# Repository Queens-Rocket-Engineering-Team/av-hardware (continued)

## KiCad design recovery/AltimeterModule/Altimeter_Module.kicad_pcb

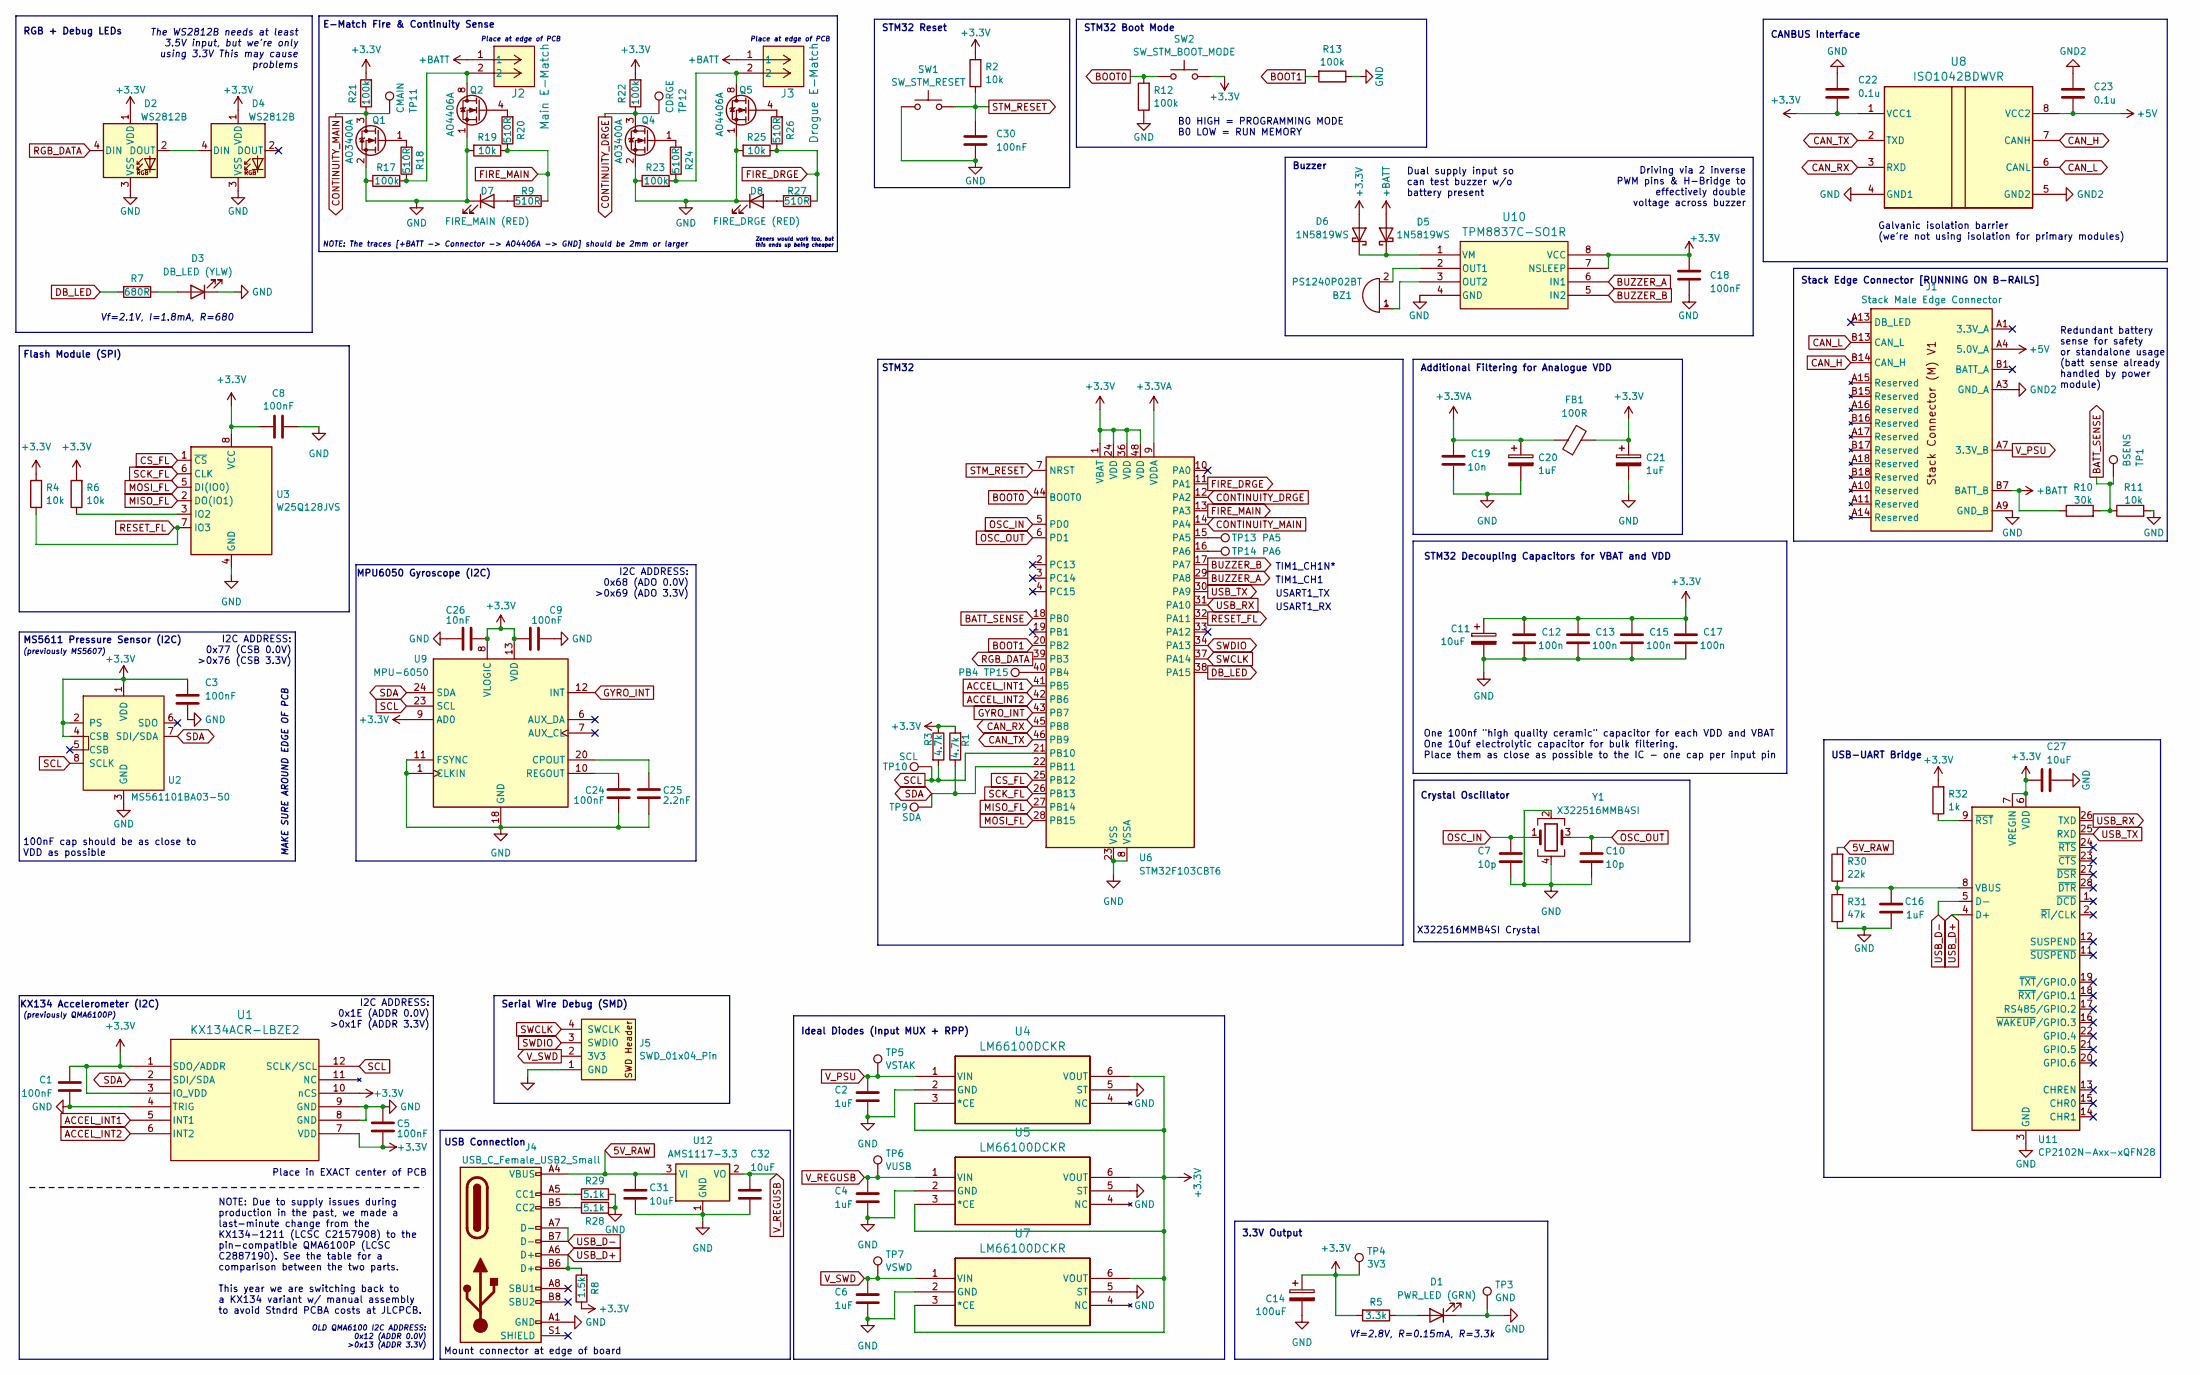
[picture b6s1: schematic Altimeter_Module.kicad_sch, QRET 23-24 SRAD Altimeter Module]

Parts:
BZ1: PS1240P02BT; Buzzer_12.6x9.5RM5.0; Digikey 445-2525-1-ND
C1, C3, C5, C8, C9, C18, C24, C30: 100nF; C_0603_1608Metric; JLCPCB C14663
C2, C4, C6, C16: 1uF; C_0603_1608Metric; JLCPCB C15849
C7, C10: 10p; C_0603_1608Metric; JLCPCB C1634
C11: 10uF; CP_Elec_4x5.4; Digikey 732-8411-1-ND
C12, C13, C15, C17: 100n; C_0402_1005Metric; JLCPCB C1525
C14: 100uF; CP_Elec_6.3x5.9; Digikey 732-8419-1-ND
C19: 10n; C_0603_1608Metric; JLCPCB C57112
C20, C21: 1uF; C_0805_2012Metric; JLCPCB C28323
C22, C23: 0.1u; C_0603_1608Metric; JLCPCB C14663
C25: 2.2nF; C_0603_1608Metric; JLCPCB C1604
C26: 10nF; C_0603_1608Metric; JLCPCB C57112
C27, C31, C32: 10uF; C_0603_1608Metric; JLCPCB C96446
D1: PWR_LED (GRN); LED_0805_2012Metric; JLCPCB C2297
D2, D4: WS2812B; LED_WS2812B_PLCC4_5.0x5.0mm_P3.2mm; Digikey 1568-COM-16347CT-ND
D3: DB_LED (YLW); LED_0603_1608Metric; JLCPCB C72038
D5, D6: 1N5819WS; D_SOD-323; JLCPCB C191023
D7: FIRE_MAIN (RED); LED_0603_1608Metric; JLCPCB C2286
D8: FIRE_DRGE (RED); LED_0603_1608Metric; JLCPCB C2286
FB1: 100R; R_0805_2012Metric; JLCPCB C1015
J1: Stack Male Edge Connector; BUS_PCIexpress_x1
J2: Main E-Match; CONN_2-1445057-2_TYCO; Digikey A33212CT-ND
J3: Drogue E-Match; CONN_2-1445057-2_TYCO; Digikey A33212CT-ND
J4: USB_C_Female_USB2_Small; USB_C_DB-108PWB; JLCPCB C5178541
J5: SWD_01x04_Pin; SWD_PinHeader_1x04_P2.54mm_Horizontal_SMD; Digikey 952-3233-ND
Q1, Q4: AO3400A; SOT-23; JLCPCB C20917
Q2, Q5: AO4406A; SOIC-8_3.9x4.9mm_P1.27mm; JLCPCB C5155213
R1, R3: 4.7k; R_0603_1608Metric; JLCPCB C23162
R2, R4, R6, R11, R19, R25: 10k; R_0603_1608Metric; JLCPCB C25804
R5: 3.3k; R_0603_1608Metric; JLCPCB C22978
R7: 680R; R_0603_1608Metric; JLCPCB C23228
R8: 1.5k; R_0603_1608Metric; JLCPCB C22843
R9, R18, R20, R24, R26, R27: 510R; R_0603_1608Metric; JLCPCB C23193
R10: 30k; R_0603_1608Metric; JLCPCB C22984
R12, R13, R17, R21, R22, R23: 100k; R_0603_1608Metric; JLCPCB C25803
R28, R29: 5.1k; R_0603_1608Metric; JLCPCB C23186
R30: 22k; R_0603_1608Metric; JLCPCB C31850
R31: 47k; R_0603_1608Metric; JLCPCB C25819
R32: 1k; R_0603_1608Metric; JLCPCB C21190
SW1: SW_STM_RESET; SW_Push_1P1T_XKB_TS-1187A; JLCPCB C318884
SW2: SW_STM_BOOT_MODE; SW_Push_1P1T_XKB_TS-1187A; JLCPCB C318884
TP1: BSENS; TestPoint_Pad_1.5x1.5mm
TP3: GND; TestPoint_Pad_1.5x1.5mm
TP4: 3V3; TestPoint_Pad_1.5x1.5mm
TP5: VSTAK; TestPoint_Pad_1.5x1.5mm
TP6: VUSB; TestPoint_Pad_1.5x1.5mm
TP7: VSWD; TestPoint_Pad_1.5x1.5mm
TP9: SDA; TestPoint_Pad_1.5x1.5mm
TP10: SCL; TestPoint_Pad_1.5x1.5mm
TP11: CMAIN; TestPoint_Pad_1.5x1.5mm
TP12: CDRGE; TestPoint_Pad_1.5x1.5mm
TP13: PA5; TestPoint_Pad_1.5x1.5mm
TP14: PA6; TestPoint_Pad_1.5x1.5mm
TP15: PB4; TestPoint_Pad_1.5x1.5mm
U1: KX134ACR-LBZE2; LGA-12_2x2mm_P0.5mm; Digikey 846-KX134ACR-LBZE2CT-ND
U2: MS561101BA03-50; MS5607_Handsolder; Digikey 223-1622-1-ND
U3: W25Q128JVS; SOIC-8_5.23x5.23mm_P1.27mm; JLCPCB C97521
U4, U5, U7: LM66100DCKR; SC-70-6_Handsoldering; JLCPCB C2869734
U6: STM32F103CBT6; LQFP-48_7x7mm_P0.5mm; JLCPCB C8304
U8: ISO1042BDWVR; SOIC-8 ISO1042BDWV; JLCPCB C484409
U9: MPU-6050; InvenSense_QFN-24_4x4mm_P0.5mm; JLCPCB C24112
U10: TPM8837C-SO1R; SOP-8_TPK; Digikey 5503-TPM8837C-SO1RCT-ND
U11: CP2102N-Axx-xQFN28; QFN-28-1EP_5x5mm_P0.5mm_EP3.35x3.35mm; JLCPCB C6568
U12: AMS1117-3.3; SOT-223-3_TabPin2; JLCPCB C6186
Y1: X322516MMB4SI; Crystal_SMD_3225-4Pin_3.2x2.5mm; JLCPCB C13738

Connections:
5V_RAW: C31.1, J4.A4 (VBUS), J4.A9 (VBUS), J4.B4 (VBUS), J4.B9 (VBUS), R30.2, U12.3 (VI)
+3.3V: C1.1, C3.1, C5.2, C8.1, C9.1, C11.1, C12.1, C13.1, C14.1, C15.1, C17.1, C18.1, C21.1, C22.2, C26.1, C27.2, D2.1 (VDD), D4.1 (VDD), D6.2 (A), FB1.2, R1.2, R2.2, R3.1, R4.2, R5.2, R6.2, R8.1, R21.2, R22.2, R32.2, SW2.2, TP4.1, U1.1 (SDO/ADDR), U1.3 (IO_VDD), U1.7 (VDD), U1.10 (nCS), U2.1 (VDD), U2.2 (PS), U2.4 (CSB), U3.8 (VCC), U4.3 (*CE), U4.6 (VOUT), U5.3 (*CE), U5.6 (VOUT), U6.1 (VBAT), U6.24 (VDD), U6.36 (VDD), U6.48 (VDD), U7.3 (*CE), U7.6 (VOUT), U8.1 (VCC1), U9.8 (VLOGIC), U9.9 (AD0), U9.13 (VDD), U10.7 (NSLEEP), U10.8 (VCC), U11.6 (VDD), U11.7 (VREGIN)
+3.3VA: C19.1, C20.1, FB1.1, U6.9 (VDDA)
+5V: C23.2, J1.A4 (5.0V_A), J1.A5 (5.0V_A), U8.8 (VCC2)
+BATT: D5.2 (A), J1.B7 (BATT_B), J1.B8 (BATT_B), J1.B9 (BATT_B), J2.1, J3.1, R10.1
ACCEL_INT1: U1.5 (INT1), U6.41 (PB5)
ACCEL_INT2: U1.6 (INT2), U6.42 (PB6)
BATT_SENSE: R10.2, R11.1, TP1.1, U6.18 (PB0)
BOOT0: R12.2, SW2.1, U6.44 (BOOT0)
BOOT1: R13.2, U6.20 (PB2)
BUZZER_A: U6.29 (PA8), U10.6 (IN1)
BUZZER_B: U6.17 (PA7), U10.5 (IN2)
CAN_H: J1.B14 (CAN_H), U8.7 (CANH)
CAN_L: J1.B13 (CAN_L), U8.6 (CANL)
CAN_RX: U6.45 (PB8), U8.3 (RXD)
CAN_TX: U6.46 (PB9), U8.2 (TXD)
CONTINUITY_DRGE: Q4.3 (D), R22.1, TP12.1, U6.12 (PA2)
CONTINUITY_MAIN: Q1.3 (D), R21.1, TP11.1, U6.14 (PA4)
CS_FL: U3.1 (~CS), U6.25 (PB12)
DB_LED: R7.2, U6.38 (PA15)
FIRE_DRGE: R25.1, R26.1, R27.1, U6.11 (PA1)
FIRE_MAIN: R9.1, R19.1, R20.1, U6.13 (PA3)
GND: C1.2, C2.2, C3.2, C4.2, C5.1, C6.2, C7.2, C8.2, C9.2, C10.2, C11.2, C12.2, C13.2, C14.2, C15.2, C16.1, C17.2, C18.2, C19.2, C20.2, C21.2, C22.1, C24.2, C25.2, C26.2, C27.1, C30.2, C31.2, C32.2, D1.1 (K), D2.3 (VSS), D3.1 (K), D4.3 (VSS), D7.1 (K), D8.1 (K), J1.A9 (GND_B), J1.A12 (GND_B), J1.B10 (GND_B), J1.B11 (GND_B), J1.B12 (GND_B), J4.A1 (GND), J4.A12 (GND), J4.B1 (GND), J4.B12 (GND), J5.1 (GND), Q1.2 (S), Q2.1 (S), Q2.2 (S), Q2.3 (S), Q4.2 (S), Q5.1 (S), Q5.2 (S), Q5.3 (S), R11.2, R12.1, R13.1, R17.1, R19.2, R23.1, R25.2, R28.2, R29.2, R31.1, SW1.1, TP3.1, U1.4 (TRIG), U1.8 (GND), U1.9 (GND), U2.3 (GND), U3.4 (GND), U4.2 (GND), U4.5 (ST), U5.2 (GND), U5.5 (ST), U6.8 (VSSA), U6.23 (VSS), U6.35 (VSS), U6.47 (VSS), U7.2 (GND), U7.5 (ST), U8.4 (GND1), U9.1 (CLKIN), U9.11 (FSYNC), U9.18 (GND), U10.4 (GND), U11.3 (GND), U11.29 (GND), U12.1 (GND), Y1.2, Y1.4
GND2: C23.1, J1.A3 (GND_A), J1.A6 (GND_A), J1.B4 (GND_A), J1.B5 (GND_A), J1.B6 (GND_A), U8.5 (GND2)
GYRO_INT: U6.43 (PB7), U9.12 (INT)
MISO_FL: U3.2 (DO(IO1)), U6.27 (PB14)
MOSI_FL: U3.5 (DI(IO0)), U6.28 (PB15)
unnamed: BZ1.2 (+), U10.2 (OUT1)
unnamed: BZ1.1 (-), U10.3 (OUT2)
unnamed: D1.2 (A), R5.1
unnamed: D2.2 (DOUT), D4.4 (DIN)
unnamed: D3.2 (A), R7.1
unnamed: D5.1 (K), D6.1 (K), U10.1 (VM)
unnamed: D7.2 (A), R9.2
unnamed: D8.2 (A), R27.2
unnamed: J2.2, Q2.5 (D), Q2.6 (D), Q2.7 (D), Q2.8 (D), R17.2, R18.1
unnamed: J3.2, Q5.5 (D), Q5.6 (D), Q5.7 (D), Q5.8 (D), R23.2, R24.1
unnamed: J4.A5 (CC1), R29.1
unnamed: J4.B5 (CC2), R28.1
unnamed: Q1.1 (G), R18.2
unnamed: Q2.4 (G), R20.2
unnamed: Q4.1 (G), R24.2
unnamed: Q5.4 (G), R26.2
unnamed: R6.1, U3.3 (IO2)
unnamed: TP13.1, U6.15 (PA5)
unnamed: TP14.1, U6.16 (PA6)
unnamed: TP15.1, U6.40 (PB4)
unnamed: C25.1, U9.20 (CPOUT)
unnamed: C24.1, U9.10 (REGOUT)
unnamed: C16.2, R30.1, R31.2, U11.8 (VBUS)
unnamed: R32.1, U11.9 (~RST)
OSC_IN: C7.1, U6.5 (PD0), Y1.1
OSC_OUT: C10.1, U6.6 (PD1), Y1.3
RESET_FL: R4.1, U3.7 (IO3), U6.32 (PA11)
RGB_DATA: D2.4 (DIN), U6.39 (PB3)
SCK_FL: U3.6 (CLK), U6.26 (PB13)
SCL: R3.2, TP10.1, U1.12 (SCLK/SCL), U2.8 (SCLK), U6.21 (PB10), U9.23 (SCL)
SDA: R1.1, TP9.1, U1.2 (SDI/SDA), U2.7 (SDI/SDA), U6.22 (PB11), U9.24 (SDA)
STM_RESET: C30.1, R2.1, SW1.2, U6.7 (NRST)
SWCLK: J5.4 (SWCLK), U6.37 (PA14)
SWDIO: J5.3 (SWDIO), U6.34 (PA13)
USB_D+: J4.A6 (D+), J4.B6 (D+), R8.2, U11.4 (D+)
USB_D-: J4.A7 (D-), J4.B7 (D-), U11.5 (D-)
USB_RX: U6.31 (PA10), U11.26 (TXD)
USB_TX: U6.30 (PA9), U11.25 (RXD)
V_PSU: C2.1, J1.A7 (3.3V_B), J1.A8 (3.3V_B), TP5.1, U4.1 (VIN)
V_REGUSB: C4.1, C32.1, TP6.1, U5.1 (VIN), U12.2 (VO)
V_SWD: C6.1, J5.2 (3V3), TP7.1, U7.1 (VIN)

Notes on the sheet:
Serial Wire Debug (SMD)
Flash Module (SPI)
RGB + Debug LEDs
The WS2812B needs at least 3.5V input, but we're only using 3.3V This may cause problems
Additional Filtering for Analogue VDD
(previously QMA6100P)
Stack Edge Connector [RUNNING ON B-RAILS]
NOTE: Due to supply issues during production in the past, we made a last-minute change from the KX134-1211 (LCSC C2157908) to the pin-compatible QMA6100P (LCSC C2887190). See the table for a comparison between the two parts. This year we are switching back to a KX134 variant w/ manual assembly to a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
Buzzer
Place at edge of PCB
Ideal Diodes (Input MUX + RPP)
Crystal Oscillator
Vf=2.1V, I=1.8mA, R=680
STM32
I2C ADDRESS: 0x1E (ADDR 0.0V) >0x1F (ADDR 3.3V)
B0 HIGH = PROGRAMMING MODE B0 LOW = RUN MEMORY
USART1_TX
USART1_RX
MS5611 Pressure Sensor (I2C)
Place in EXACT center of PCB
3.3V Output
OLD QMA6100 I2C ADDRESS: 0x12 (ADDR 0.0V) >0x13 (ADDR 3.3V)
Mount connector at edge of board
(previously MS5607)
X322516MMB4SI Crystal
CANBUS Interface
STM32 Decoupling Capacitors for VBAT and VDD
I2C ADDRESS: 0x68 (ADO 0.0V) >0x69 (ADO 3.3V)
STM32 Boot Mode
TIM1_CH1N*
TIM1_CH1
KX134 Accelerometer (I2C)
E-Match Fire & Continuity Sense
Galvanic isolation barrier (we're not using isolation for primary modules)
One 100nf "high quality ceramic" capacitor for each VDD and VBAT One 10uf electrolytic capacitor for bulk filtering. Place them as close as possible to the IC - one cap per input pin
NOTE: The traces [+BATT -> Connector -> AO4406A -> GND] should be 2mm or larger
Zeners would work too, but this ends up being cheaper
MAKE SURE AROUND EDGE OF PCB
Driving via 2 inverse PWM pins & H-Bridge to effectively double voltage across buzzer
100nF cap should be as close to VDD as possible

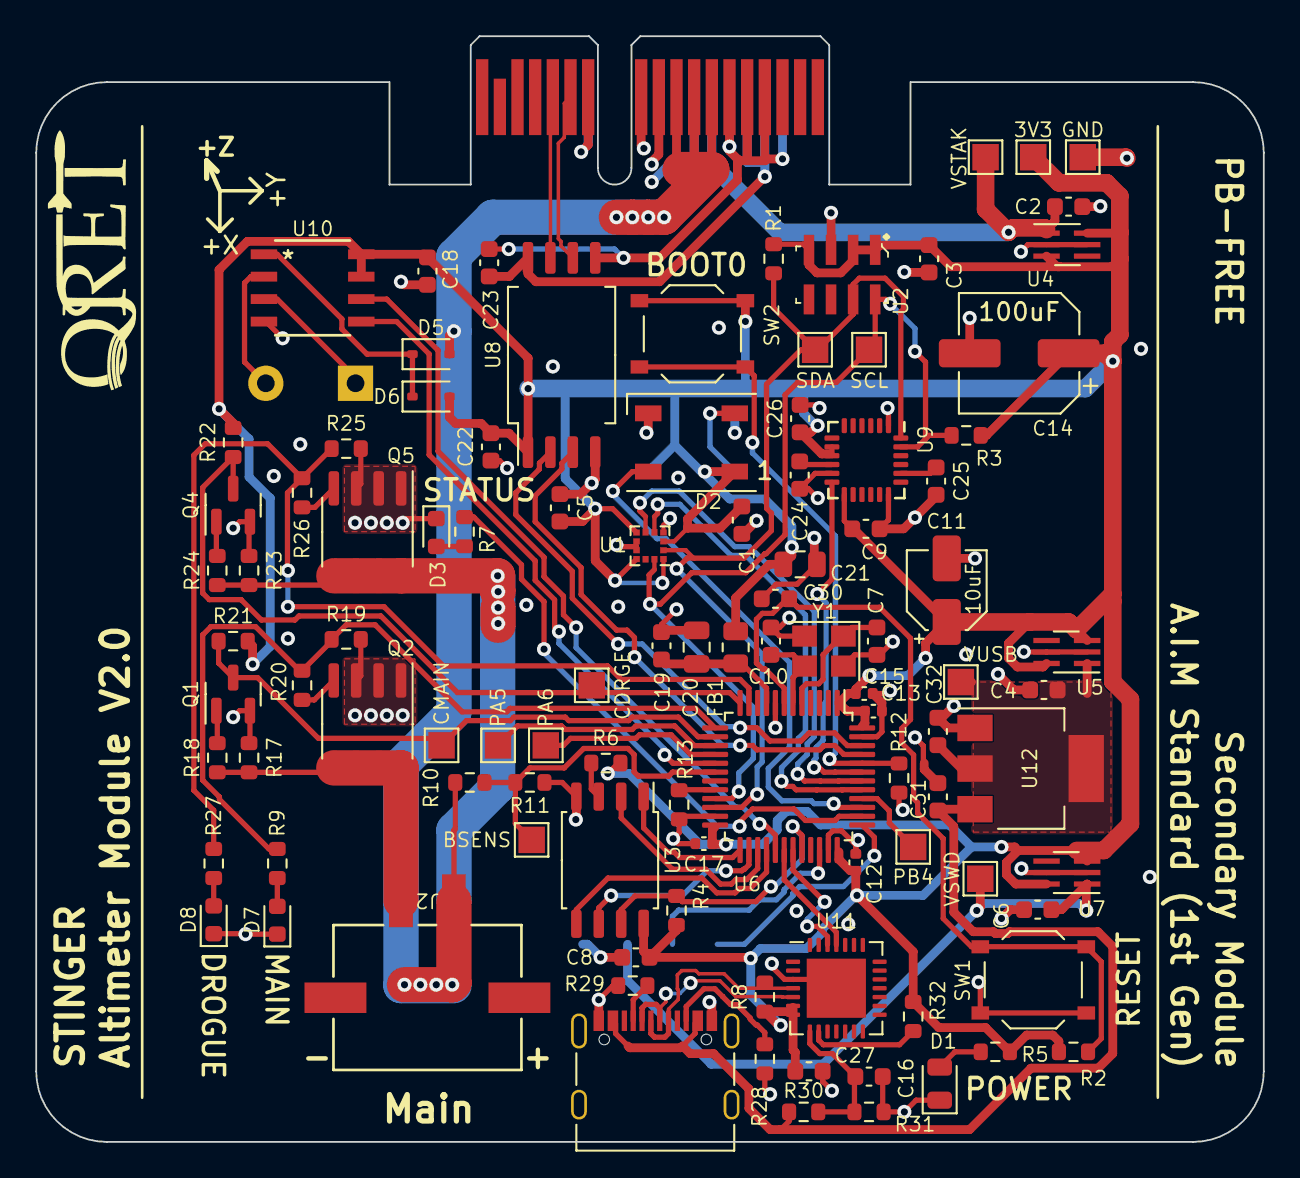
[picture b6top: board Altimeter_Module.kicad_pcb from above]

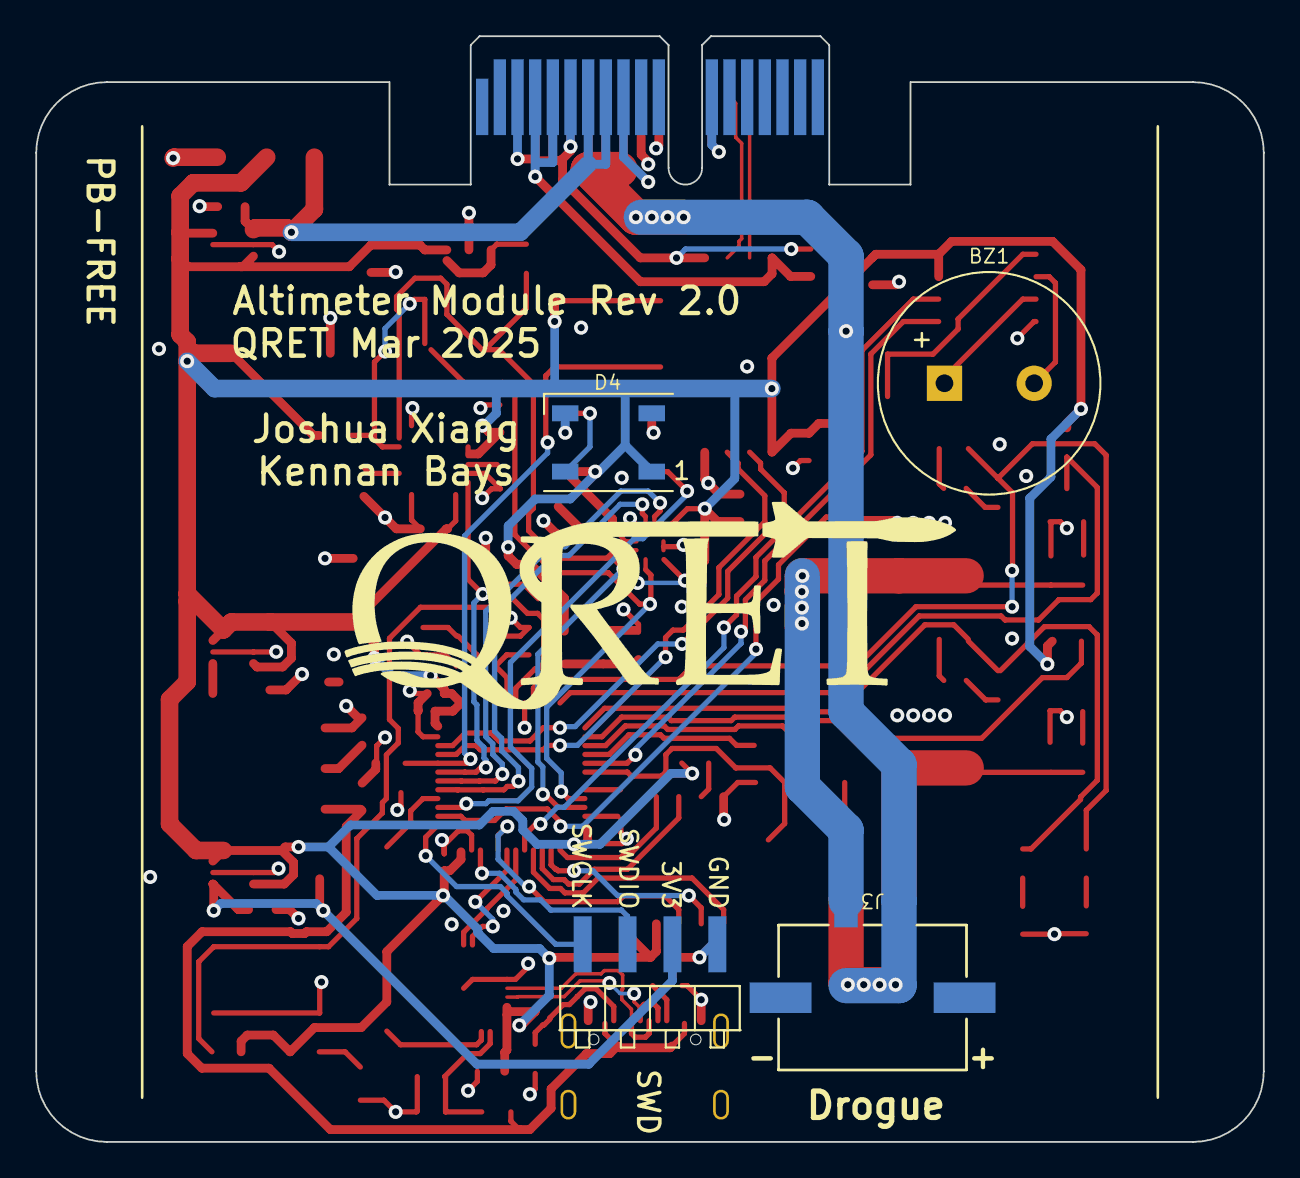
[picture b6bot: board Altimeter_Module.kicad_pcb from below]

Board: 4 copper layers, 69.5 x 62.6 mm, 106 parts (4 on the bottom side), 68 nets.

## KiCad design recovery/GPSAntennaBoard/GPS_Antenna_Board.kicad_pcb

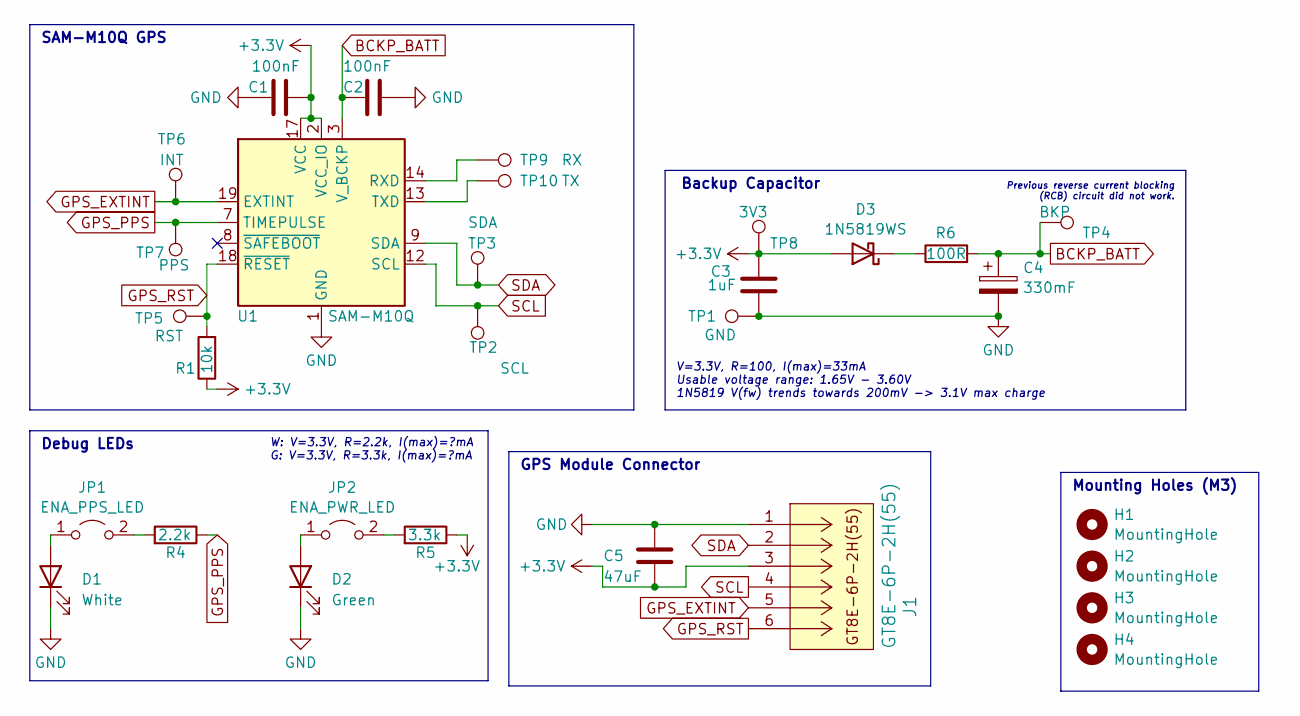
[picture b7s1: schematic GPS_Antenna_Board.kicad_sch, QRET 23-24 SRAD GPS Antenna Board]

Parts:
C1, C2: 100nF; C_0603_1608Metric; JLCPCB C14663
C3: 1uF; C_0603_1608Metric; JLCPCB C15849
C4: 330mF; CB5R5334HF-ZJP; Digikey 4688-CB5R5334HF-ZJP-ND
C5: 47uF; C_0805_2012Metric; JLCPCB C16780
D1: White; LED_0805_2012Metric; JLCPCB C34499
D2: Green; LED_0805_2012Metric; JLCPCB C2297
D3: 1N5819WS; D_SOD-323_HandSoldering; JLCPCB C191023
H1, H2, H3, H4: MountingHole; MountingHole_3.2mm_M3_DIN965_Pad
J1: GT8E-6P-2H(55); CONN_GT8E-6P-2H(55); Digikey 26-GT8E-6P-2H(55)CT-ND
JP1: ENA_PPS_LED; SolderJumper-2_P1.3mm_Open_RoundedPad1.0x1.5mm
JP2: ENA_PWR_LED; SolderJumper-2_P1.3mm_Open_RoundedPad1.0x1.5mm
R1: 10k; R_0603_1608Metric; JLCPCB C25804
R4: 2.2k; R_0603_1608Metric; JLCPCB C4190
R5: 3.3k; R_0603_1608Metric; JLCPCB C22978
R6: 100R; R_0603_1608Metric; JLCPCB C22775
TP1: GND; TestPoint_Pad_1.5x1.5mm
TP2: SCL; TestPoint_Pad_1.5x1.5mm
TP3: SDA; TestPoint_Pad_1.5x1.5mm
TP4: BKP; TestPoint_Pad_1.5x1.5mm
TP5: RST; TestPoint_Pad_1.5x1.5mm
TP6: INT; TestPoint_Pad_1.5x1.5mm
TP7: PPS; TestPoint_Pad_1.5x1.5mm
TP8: 3V3; TestPoint_Pad_1.5x1.5mm
TP9: RX; TestPoint_Pad_1.5x1.5mm
TP10: TX; TestPoint_Pad_1.5x1.5mm
U1: SAM-M10Q; ublox_SAM-M8Q_HandSolder; Digikey 672-SAM-M10Q-00BCT-ND

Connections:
+3.3V: C1.2, C3.1, C5.2, D3.2 (A), J1.3, R1.1, R5.1, TP8.1, U1.2 (VCC_IO), U1.17 (VCC)
BCKP_BATT: C2.2, C4.1, R6.2, TP4.1, U1.3 (V_BCKP)
GND: C1.1, C2.1, C3.2, C4.2, C5.1, D1.1 (K), D2.1 (K), J1.1, TP1.1, U1.1 (GND), U1.4 (GND), U1.5 (GND), U1.6 (GND), U1.10 (GND), U1.11 (GND), U1.15 (GND), U1.16 (GND), U1.20 (GND)
GPS_EXTINT: J1.5, TP6.1, U1.19 (EXTINT)
GPS_PPS: R4.1, TP7.1, U1.7 (TIMEPULSE)
GPS_RST: J1.6, R1.2, TP5.1, U1.18 (~RESET)
unnamed: D1.2 (A), JP1.1 (A)
unnamed: D2.2 (A), JP2.1 (A)
unnamed: D3.1 (K), R6.1
unnamed: JP1.2 (B), R4.2
unnamed: JP2.2 (B), R5.2
unnamed: TP9.1, U1.14 (RXD)
unnamed: TP10.1, U1.13 (TXD)
SCL: J1.4, TP2.1, U1.12 (SCL)
SDA: J1.2, TP3.1, U1.9 (SDA)

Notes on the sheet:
W: V=3.3V, R=2.2k, I(max)=?mA G: V=3.3V, R=3.3k, I(max)=?mA
Mounting Holes (M3)
V=3.3V, R=100, I(max)=33mA Usable voltage range: 1.65V - 3.60V 1N5819 V(fw) trends towards 200mV -> 3.1V max charge
Backup Capacitor
SAM-M10Q GPS
GPS Module Connector
Debug LEDs
Previous reverse current blocking (RCB) circuit did not work.

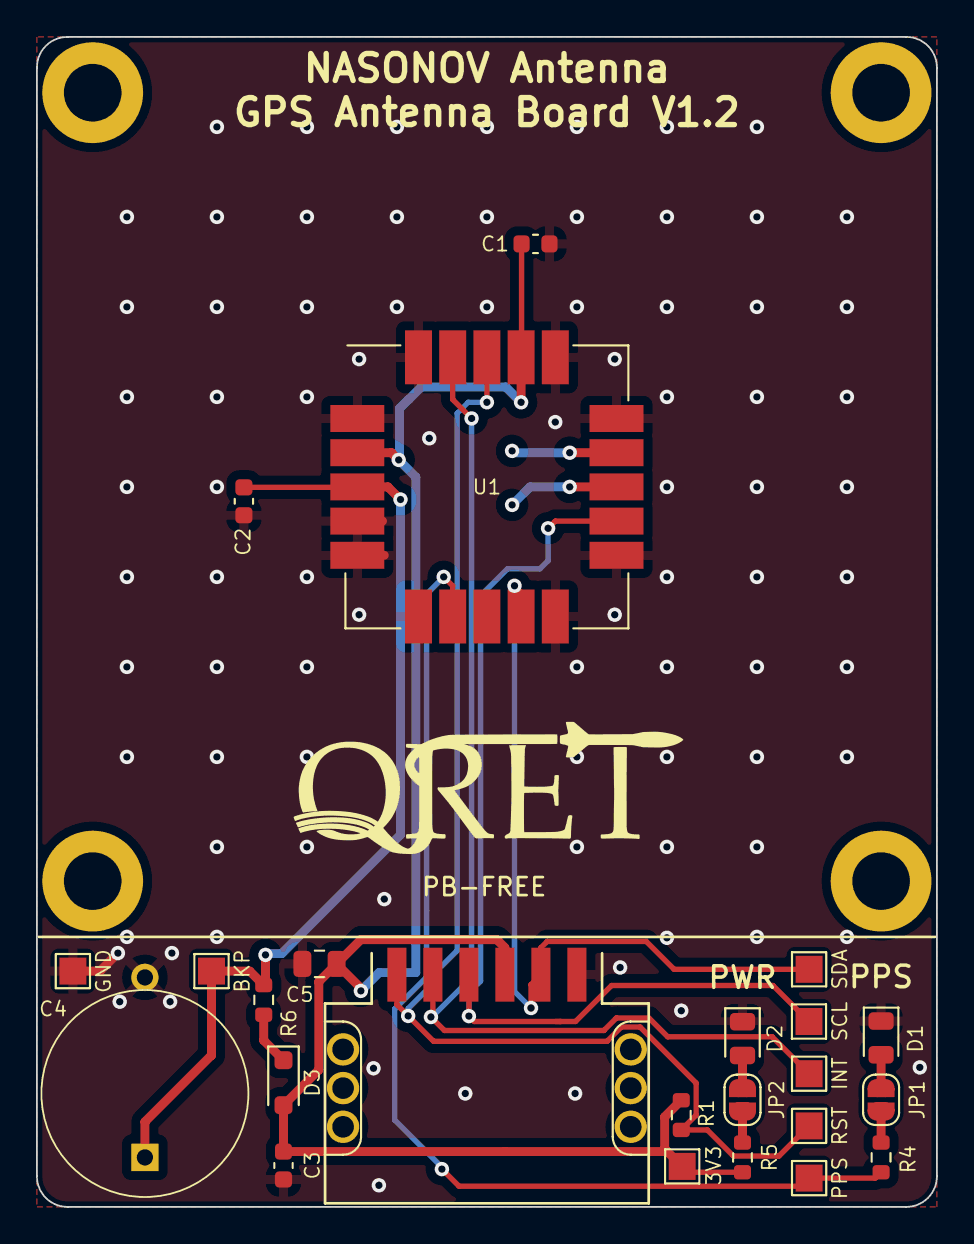
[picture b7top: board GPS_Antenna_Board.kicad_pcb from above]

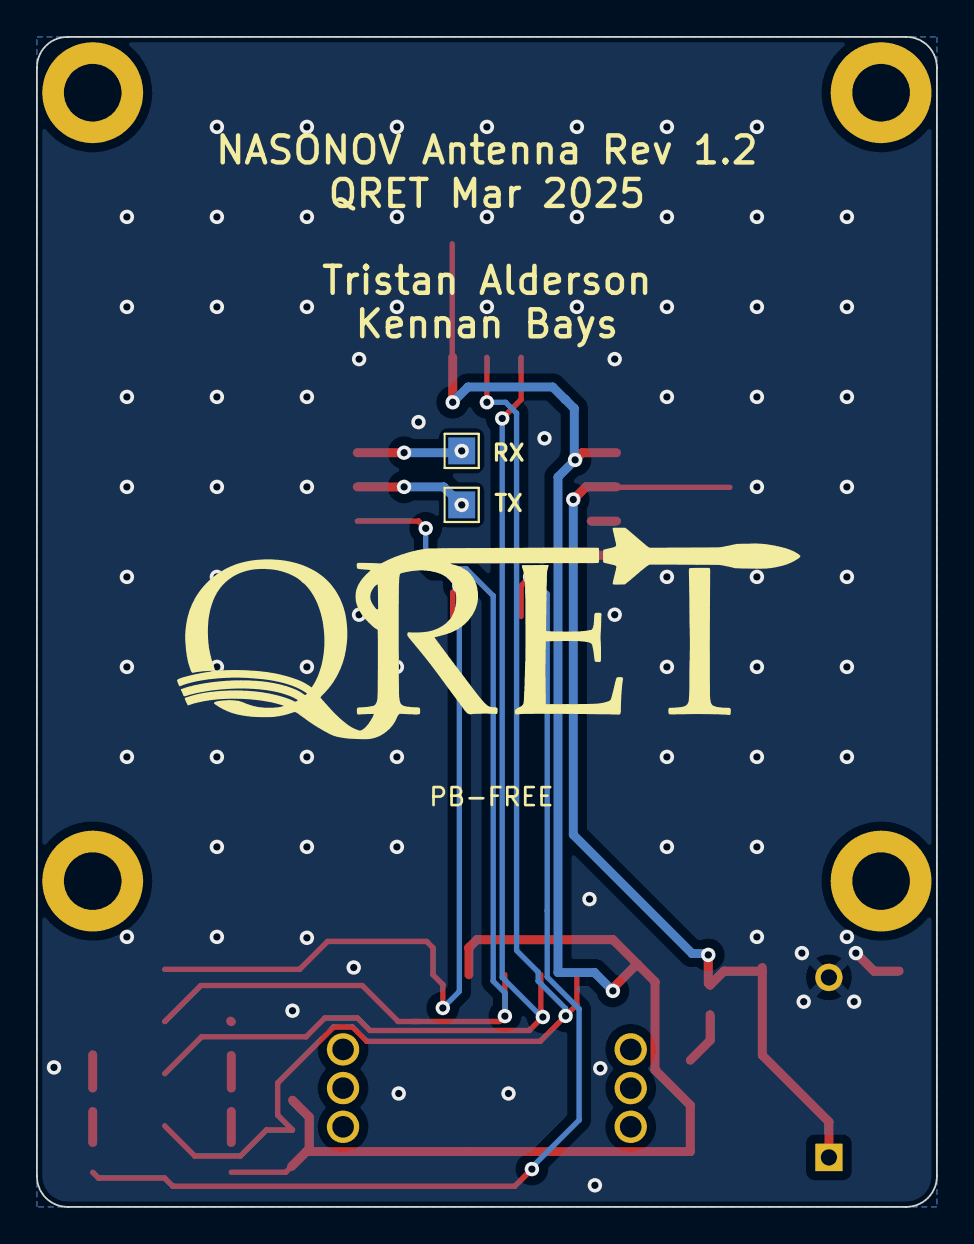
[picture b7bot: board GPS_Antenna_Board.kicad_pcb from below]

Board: 2 copper layers, 50.0 x 65.0 mm, 30 parts (2 on the bottom side), 15 nets.

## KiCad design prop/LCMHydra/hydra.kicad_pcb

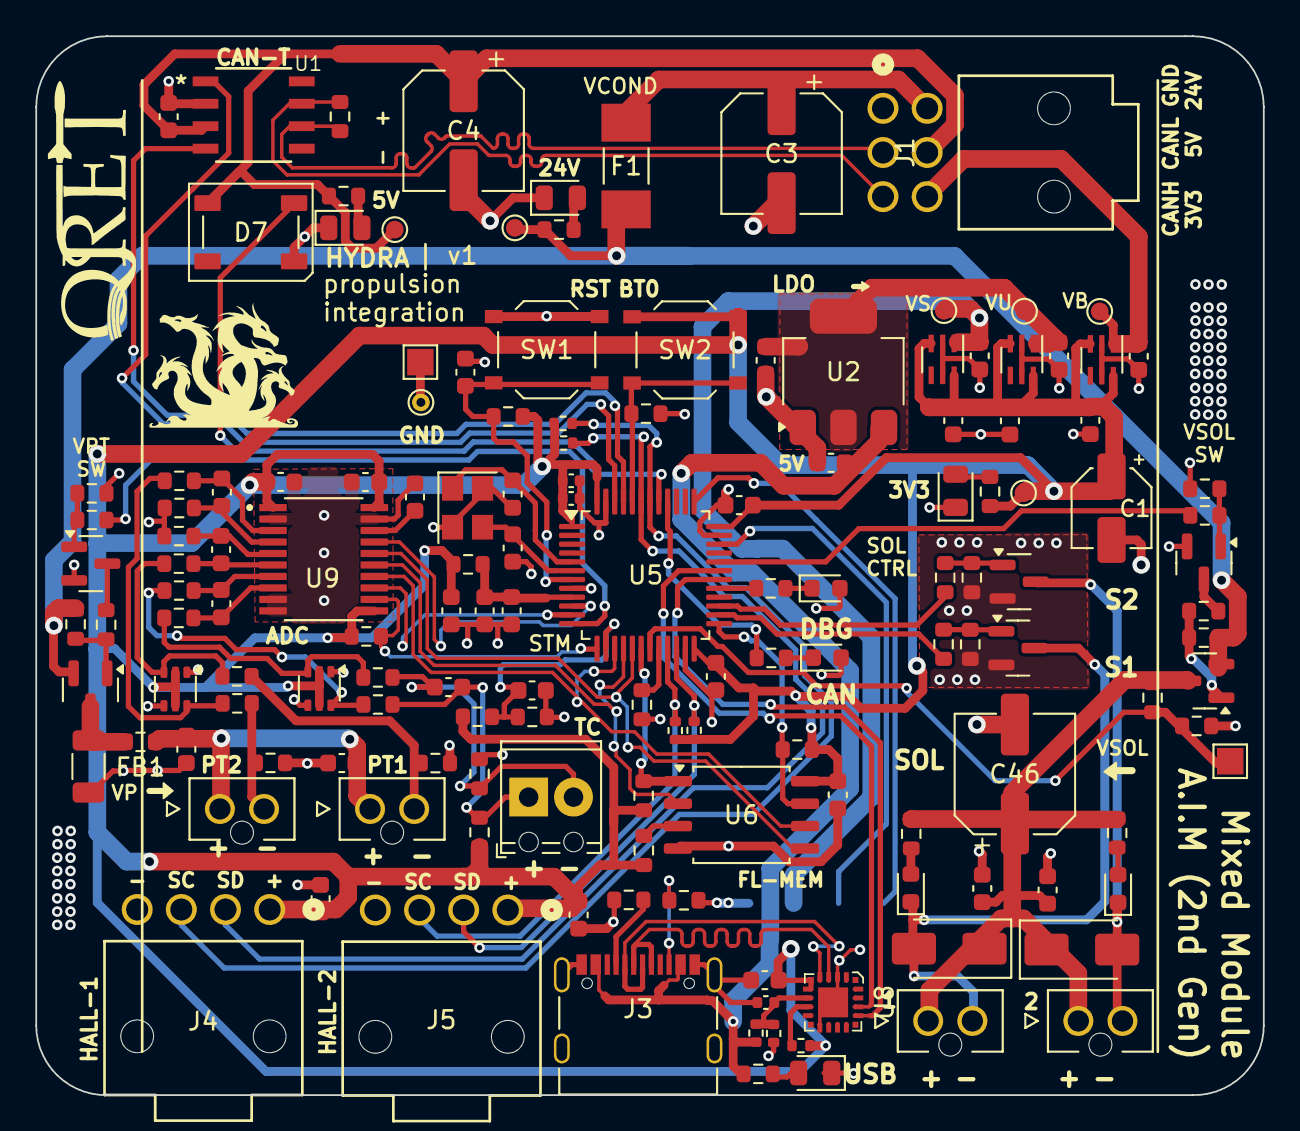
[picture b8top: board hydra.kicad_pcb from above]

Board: 4 copper layers, 69.5 x 60.0 mm, 149 parts (1 on the bottom side), 89 nets.

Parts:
C1: 10uF; CP_Elec_4x5.4
C2: 0.1uF; C_0603_1608Metric
C3, C4, C46: 100uF; CP_Elec_6.3x5.9
C5, C6, C28, C43, C44, C48, C49: 1uF; C_0603_1608Metric
C7, C12, C21, C50: 10uF; C_0603_1608Metric
C8, C9, C17, C18, C23, C30, C33, C39, C41, C45, C52: 100nF; C_0603_1608Metric
C10, C11: 10p; C_0603_1608Metric
C13, C14: 100n; C_0402_1005Metric
C15, C16: 100n; C_0603_1608Metric
C20: 1uF; C_0402_1005Metric
C26, C27, C34, C56: 10nF; C_0603_1608Metric
C29: 220 nF; C_0603_1608Metric
C35: 10uF; C_1206_3216Metric
C51: 1nF; C_0603_1608Metric
D1: PWR_3V3_LED (GRN); LED_0805_2012Metric
D2: PWR_24V_LED (GRN); LED_0805_2012Metric
D3: PWR_5V_LED (GRN); LED_0805_2012Metric
D4: USB_LED (GRN); LED_0805_2012Metric
D5: DB_LED (YLW); LED_0603_1608Metric
D6: CAN_LED (WHT); LED_0603_1608Metric
D7: SYS_LED; LED_WS2812B_PLCC4_5.0x5.0mm_P3.2mm
D11: SOL2_LED (YELW); LED_0603_1608Metric
D12: SOL1_LED (YELW); LED_0603_1608Metric
D13, D18: BAV199DW; SOT-363_SC-70-6
D15, D16: SS34; D_SMA
F1: Fuse; FUSC6125X279N
FB1, FB2: 600R; R_0603_1608Metric
J1: Conn_01x06; CONN_SD-105314-100_06_MOL
J2: SWD_CONN; SWD_PinHeader_1x04_P2.54mm_Horizontal_SMD
J3: USB_C_CONN; USB_C_DB-108PWB
J4: HALL-1; CONN_SD-105313-100_04_MOL
J5: HALL-2; CONN_SD-105313-100_04_MOL
J6, J8: PT; MOLEX_1053091102
J7: Screw_Terminal_01x02; TerminalBlock_Phoenix_MPT-0,5-2-2.54_1x02_P2.54mm_Horizontal
J9, J10: SOL_CONN; MOLEX_1053091102
Q1, Q2: AO3400A; SOT-23
Q3, Q5: 2N7002; SOT-23
R1: 3.3k; R_0603_1608Metric
R2, R30, R31: 12k; R_0603_1608Metric
R3, R16, R23, R51: 6.2k; R_0603_1608Metric
R5, R6, R7, R8, R22, R25, R43, R48, R49, R50, R52, R54, R60: 10k; R_0603_1608Metric
R9, R10: 5.1k; R_0603_1608Metric
R11: 22k; R_0402_1005Metric
R12: 47k; R_0402_1005Metric
R13: 1k; R_0402_1005Metric
R14: 680; R_0603_1608Metric
R15: 270; R_0603_1608Metric
R17, R18, R21, R45: 2.2k; R_0402_1005Metric
R19, R20: 1.2k; R_0603_1608Metric
R24, R28, R33, R37: 1k; R_0603_1608Metric
R26, R27: 1M; R_0603_1608Metric
R29, R34, R36, R38, R40, R41, R44, R53: 200; R_0603_1608Metric
R32, R35: 62; R_0603_1608Metric
R39, R42, R47: 100k; R_0603_1608Metric
R46: 120; R_0603_1608Metric
SW1: SW_STM_RESET; SW_Push_1P1T_XKB_TS-1187A
SW2: SW_STM_BOOT_MODE; SW_Push_1P1T_XKB_TS-1187A
TH1: Thermistor; R_0603_1608Metric
TP1: 24V-TP; TestPoint_Pad_D1.0mm
TP2: 3V3-TP; TestPoint_Pad_D1.0mm
TP3: GND-TP-H; TestPoint_THTPad_D1.0mm_Drill0.5mm
TP4: 3V3_BP; TestPoint_Pad_D1.0mm
TP5: GND-TP-P; TestPoint_Pad_1.5x1.5mm
TP6: 3V3_USB; TestPoint_Pad_D1.0mm
TP7: VSOL.S; TestPoint_Pad_1.5x1.5mm
TP9: V_SWD_TP; TestPoint_Pad_D1.0mm
TP13: 5V-TP; TestPoint_Pad_D1.0mm
U1: TCAN1051HGVDR; SOIC_1044BDR_TEX
U2: AMS1117-3.3; SOT-223-3_TabPin2
U3, U4, U10: ID_LM66100DCKR; SC-70-6
U5: STM32F103CBT6; LQFP-48_7x7mm_P0.5mm
U6: BY25Q128ES; SOIC-8_5.23x5.23mm_P1.27mm
U8: CP2102N-Axx-xQFN20; QFN-20-1EP_3x3mm
U9: ADC_ADS131M04IPWR; SOP65P640X120-20N
U11, U12: DMP4065S-7; SOT-23
Y1: X322516MMB4SI; Crystal_SMD_3225-4Pin_3.2x2.5mm

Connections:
5V_USB: C7.1, J3.A4 (VBUS), J3.A9 (VBUS), J3.B4 (VBUS), J3.B9 (VBUS), R11.2, R16.1, U2.3 (VI)
+3.3VA: C45.2, C48.2, FB2.1, U5.9 (VDDA)
+3V3: C1.1, C13.1, C14.1, C15.1, C16.1, C17.1, C21.2, C23.1, C28.2, C33.1, C43.2, C49.1, C50.1, C51.1, C52.1, D13.2 (K2), D13.5 (K4), D18.2 (K2), D18.5 (K4), FB2.2, J4.1, J5.1, R1.1, R6.2, R7.2, R8.2, R13.2, R17.2, R18.1, R21.2, R25.2, R26.1, R45.1, R48.1, R49.2, SW2.2, TP2.1, U3.3 (*CE), U3.6 (VOUT), U4.3 (*CE), U4.6 (VOUT), U5.1 (VBAT), U5.24 (VDD), U5.36 (VDD), U5.48 (VDD), U6.8 (VCC), U8.6 (VDD), U8.7 (VREGIN), U9.1 (AVDD), U9.11 (~SYNC/~RESET), U9.20 (DVDD), U10.3 (*CE), U10.6 (VOUT)
+5V: C4.1, C9.2, D7.1 (VDD), J1.5, R3.2, TP13.1, U1.3 (VCC)
+24V: F1.1, R2.2, R23.2, R51.2, TP1.1, U11.2 (S), U12.2 (S)
+24V_BP: C3.1, F1.2, J1.4
/Power Circuitry/3V3_BP: C5.2, J1.6, TP4.1, U3.1 (VIN)
/Power Circuitry/3V3_USB: C6.1, C12.1, TP6.1, U2.2 (VO), U4.1 (VIN)
/Sensing Circuitry/PT1_CLAMPED: C26.2, R34.1, U9.3 (AIN0P)
/Sensing Circuitry/PT2_CLAMPED: C27.2, R38.1, U9.6 (AIN1P)
/Sensing Circuitry/TC_N_1: C30.1, J7.2, R27.1, R28.2
/Sensing Circuitry/TC_N_CLAMPED_1: C56.1, R40.2, U9.8 (AIN2N)
/Sensing Circuitry/TC_P_1: C30.2, J7.1, R24.2, R26.2
/Sensing Circuitry/TC_P_CLAMPED_1: C56.2, R29.2, U9.7 (AIN2P)
/Sensing Circuitry/VPT: C18.1, J6.1, J8.1
/Valve Control Circuitry/VSOL: C46.1, R47.1, U12.3 (D)
ADC_CLKIN: U5.10 (PA0), U9.17 (CLKIN)
ADC_CS: R49.1, U5.13 (PA3), U9.12 (~CS)
ADC_DRDY: U5.11 (PA1), U9.13 (~DRDY)
BOOT0: R5.2, SW2.1, U5.44 (BOOT0)
BOOT1: R60.2, U5.20 (PB2)
CAN_LED: R15.1, U5.40 (PB4)
CAN_N: J1.2, R46.1, U1.6 (CANL)
CAN_P: J1.3, R46.2, U1.7 (CANH)
CAN_RX: U1.4 (RXD), U5.45 (PB8)
CAN_TX: U1.1 (TXD), U5.46 (PB9)
CJC_SENSE: C34.2, R25.1, TH1.1, U5.14 (PA4)
DB_LED: R14.1, U5.29 (PA8)
FL_CS: R48.2, U5.18 (PB0), U6.1 (~CS)
GND: C1.2, C2.2, C3.2, C4.2, C5.1, C6.2, C7.2, C8.2, C9.1, C10.2, C11.2, C12.2, C13.2, C14.2, C15.2, C16.2, C17.2, C18.2, C20.1, C21.1, C23.2, C28.1, C29.2, C33.2, C34.1, C35.2, C39.2, C41.2, C43.1, C44.2, C45.1, C46.2, C48.1, C49.2, C50.2, C51.2, C52.2, D1.1 (K), D2.1 (K), D3.1 (K), D4.1 (K), D5.2 (A), D6.2 (A), D7.3 (VSS), D13.1 (A1), D13.4 (A3), D18.1 (A1), D18.4 (A3), J1.1, J2.1 (GND), J3.A1 (GND), J3.A12 (GND), J3.B1 (GND), J3.B12 (GND), J3.S1 (SHIELD), J4.4, J5.4, Q1.2 (S), Q2.2 (S), Q3.2 (S), Q5.2 (S), R5.1, R9.2, R10.2, R12.1, R19.1, R20.1, R27.2, R32.1, R35.1, R39.1, R42.1, R43.1, R52.1, R54.1, R60.1, SW1.1, TH1.2, TP3.1, TP5.1, U1.2 (GND), U2.1 (ADJ), U3.2 (GND), U3.5 (ST), U4.2 (GND), U4.5 (ST), U5.8 (VSSA), U5.23 (VSS), U5.35 (VSS), U5.47 (VSS), U6.4 (GND), U8.3 (GND), U8.12 (GND), U8.21 (GND), U9.2 (AGND), U9.9 (AIN3N), U9.10 (AIN3P), U9.19 (DGND), U10.2 (GND), U10.5 (ST), Y1.2, Y1.4
HALL_SCL1: J4.3, R18.2, U5.43 (PB7)
HALL_SCL2: J5.3, R45.2, U5.22 (PB11)
HALL_SDA1: J4.2, R17.1, U5.42 (PB6)
HALL_SDA2: J5.2, R21.1, U5.21 (PB10)
unnamed: D1.2 (A), R1.2
unnamed: D2.2 (A), R2.1
unnamed: D3.2 (A), R3.1
unnamed: D4.2 (A), R16.2
unnamed: D5.1 (K), R14.2
unnamed: D6.1 (K), R15.2
unnamed: D11.2 (A), R30.1
unnamed: D12.2 (A), R31.1
unnamed: D13.6 (K3A4), R33.2, R34.2
unnamed: D13.3 (K1A2), R37.2, R38.2
unnamed: D18.6 (K3A4), R24.1, R29.1
unnamed: D18.3 (K1A2), R28.1, R40.1
unnamed: J3.A5 (CC1), R9.1
unnamed: J3.B5 (CC2), R10.1
unnamed: J6.2, R32.2, R33.1
unnamed: J8.2, R35.2, R37.1
unnamed: Q1.1 (G), R36.1, R39.2
unnamed: Q2.1 (G), R41.1, R42.2
unnamed: Q3.3 (D), R22.1
unnamed: Q3.1 (G), R43.2, R44.2
unnamed: Q5.3 (D), R50.1
unnamed: Q5.1 (G), R52.2, R53.2
unnamed: R8.1, U6.3 (IO2)
unnamed: C20.2, R11.1, R12.2, U8.8 (VBUS)
unnamed: R13.1, U8.9 (~RST)
unnamed: C26.1, R19.2, U9.4 (AIN0N)
unnamed: C27.1, R20.2, U9.5 (AIN1N)
unnamed: C29.1, U9.18 (CAP)
unnamed: C35.1, FB1.2, U11.3 (D)
unnamed: R22.2, R23.1, U11.1 (G)
unnamed: R50.2, R51.1, U12.1 (G)
OSC_IN: C10.1, U5.5 (PD0), Y1.1
OSC_OUT: C11.1, U5.6 (PD1), Y1.3
RESET_FL: R7.1, U5.25 (PB12), U6.7 (IO3)
RGB_DATA: D7.4 (DIN), U5.41 (PB5)
SOL1_EN: R36.2, U5.26 (PB13)
SOL1_RET: D12.1 (K), D16.2 (A), J10.2, Q1.3 (D)
SOL2_EN: R41.2, U5.27 (PB14)
SOL2_RET: D11.1 (K), D15.2 (A), J9.2, Q2.3 (D)
SPI_MISO: U5.16 (PA6), U6.2 (DO(IO1)), U9.15 (DOUT)
SPI_MOSI: U5.17 (PA7), U6.5 (DI(IO0)), U9.16 (DIN)
SPI_SCLK: U5.15 (PA5), U6.6 (CLK), U9.14 (SCLK)
STM_RESET: C8.1, R6.1, SW1.2, U5.7 (NRST)
SWCLK: J2.4 (SWCLK), U5.37 (PA14)
SWDIO: J2.3 (SWDIO), U5.34 (PA13)
USART_RX: U5.31 (PA10), U8.18 (TXD)
USART_TX: U5.30 (PA9), U8.17 (RXD)
USB_N: J3.A7 (D-), J3.B7 (D-), U8.5 (D-)
USB_P: J3.A6 (D+), J3.B6 (D+), U8.4 (D+)
VPT: C2.1, FB1.1
VPT_EN: R44.1, U5.12 (PA2)
VSOL: C39.1, C41.1, D15.1 (K), D16.1 (K), J9.1, J10.1, R30.2, R31.2
VSOL_EN: R53.1, U5.32 (PA11)
VSOL_SENSE: R47.2, R54.2, TP7.1, U5.19 (PB1)
V_SWD: C44.1, TP9.1, U10.1 (VIN)
